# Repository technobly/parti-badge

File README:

# #PartiBadge

The #PartiBadge is a Wi-Fi connected, full-featured, Particle Photon powered conference badge. Because who want to wear a piece of plastic around their neck when they can wear a PCB?

The #PartiBadge was designed by the Particle team and is currently used as an interactive learning platform for conferences and other developer events.

For workshop hands-on labs and other details, click [here](https://bit.ly/tc-workshop).

The hardware folder contains Eagle design files for iterations of the badge hardware. The firmware folder contains firmware for the latest version of the badge.

The finished badge includes:

1. A 1" OLED Screen
2. An SMD Piezo buzzer
3. A SPDT Switch
4. A 5-way joystick
5. An SMD Si7021 temperature and Humidity sensor
6. 4 Tactile LED Buttons in Red, Blue, Green and Yellow/Orange
7. An I2C-Compatible breakout for #BadgeLife add-ons
8. An IR Receiver

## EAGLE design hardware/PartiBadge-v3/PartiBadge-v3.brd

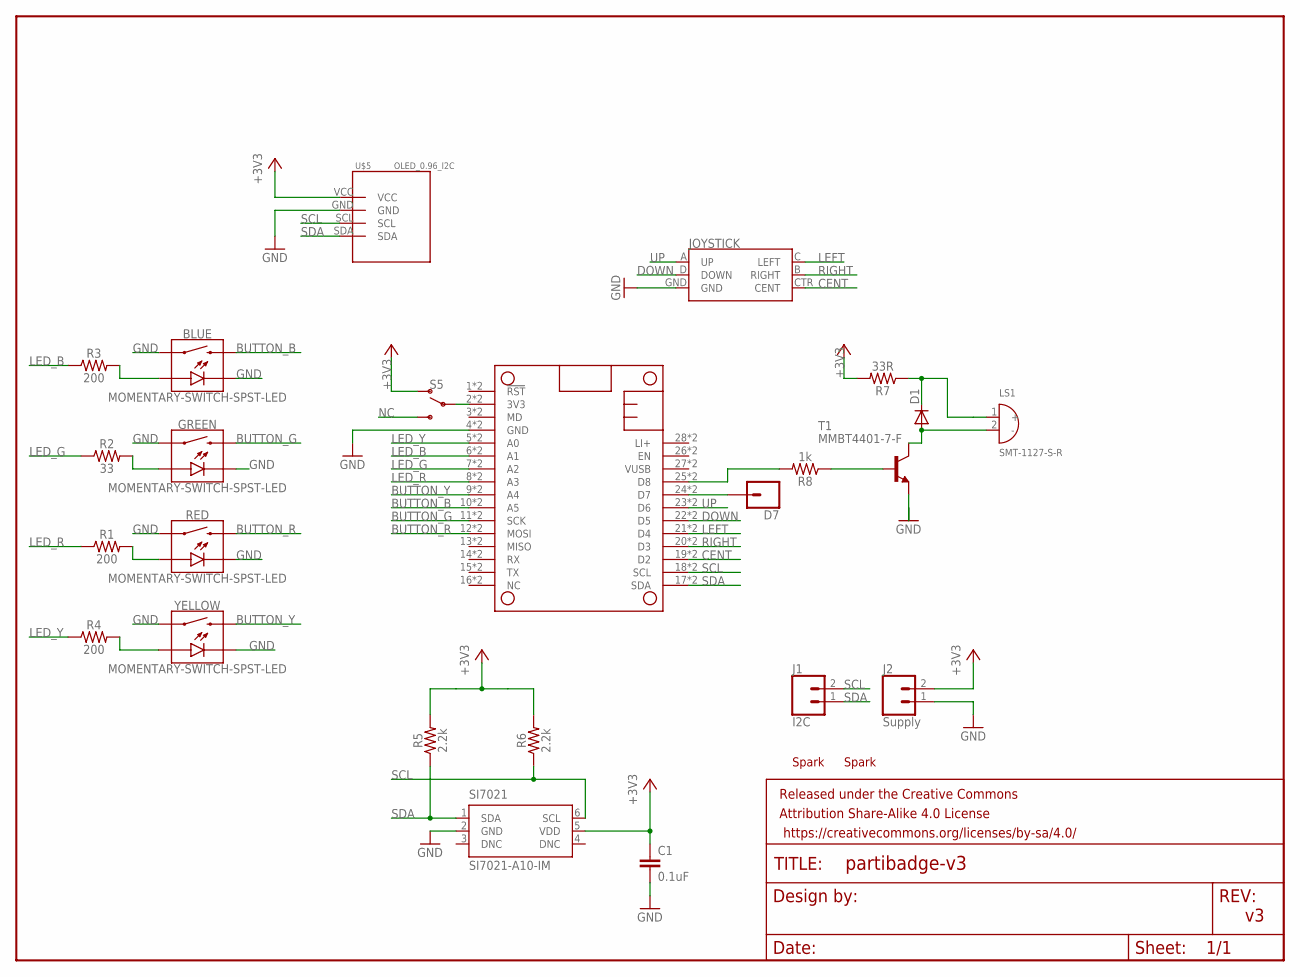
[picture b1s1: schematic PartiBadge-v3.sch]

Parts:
BLUE: MOMENTARY-SWITCH-SPST-LED; TACTILE_SWITCH_LED_PTH_12MM_KIT
C1: 0.1uF; 0603
D1: DIODE-SOD323-W; SOD323-W
D7: CONN_01; 1X01
GREEN: MOMENTARY-SWITCH-SPST-LED; TACTILE_SWITCH_LED_PTH_12MM_KIT
J1: I2C; 1X02
J2: Supply; 1X02
JOYSTICK: JOYSTICK_MINI
LS1: SMT-1127-S-R; XDCR_SMT-1127-S-R
MS1: PARTICLE_MESH_SMTDUAL; FEATHERWING_SMT2
PARTIFRAME: FRAME-LETTERNO_PACKAGE; DUMMY
R1, R3, R4: 200; 1206
R2: 33; 1206
R5, R6: 2.2k; 0603
R7: 33R; 0603
R8: 1k; 0603
RED: MOMENTARY-SWITCH-SPST-LED; TACTILE_SWITCH_LED_PTH_12MM_KIT
S5: SWITCH-SPDT-PTH-11.6X4.0MM; SWITCH_SPDT_PTH_11.6X4.0MM
SI7021: SI7021-A10-IM; DFN6-3X3
T1: MMBT4401-7-F; SOT23-BEC
U$1, U$2: SPARK_LOGO_WITH_PLANE; SPARK_LOGO_PLUS_PLANE
U$5: OLED_0.96_I2C
YELLOW: MOMENTARY-SWITCH-SPST-LED; TACTILE_SWITCH_LED_PTH_12MM_KIT

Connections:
3V3: MS1.2 (3V3), MS1.2' (3V3), S5.2
+3V3: C1.1, J2.2, R5.2, R6.2, R7.2, S5.1 (O), SI7021.5 (VDD), U$5.VCC
BUTTON_B: BLUE.2, MS1.10 (A5), MS1.10' (A5)
BUTTON_G: GREEN.2, MS1.11 (SCK), MS1.11' (SCK)
BUTTON_R: MS1.12 (MOSI), MS1.12' (MOSI), RED.2
BUTTON_Y: MS1.9 (A4), MS1.9' (A4), YELLOW.2
CENT: JOYSTICK.CTR (CENT), MS1.19 (D2), MS1.19' (D2)
DOWN: JOYSTICK.D (DOWN), MS1.22 (D5), MS1.22' (D5)
GND: BLUE.4 (1), BLUE.C, C1.2, GREEN.4 (1), GREEN.C, J2.1, JOYSTICK.GND, MS1.4 (GND), MS1.4' (GND), RED.4 (1), RED.C, SI7021.2 (GND), T1.E, U$5.GND, YELLOW.4 (1), YELLOW.C
LED_B: MS1.6 (A1), MS1.6' (A1), R3.1
LED_G: MS1.7 (A2), MS1.7' (A2), R2.1
LED_R: MS1.8 (A3), MS1.8' (A3), R1.1
LED_Y: MS1.5 (A0), MS1.5' (A0), R4.1
LEFT: JOYSTICK.C (LEFT), MS1.21 (D4), MS1.21' (D4)
unnamed: D7.1, MS1.24 (D7), MS1.24' (D7)
unnamed: MS1.25 (D8), MS1.25' (D8), R8.2
unnamed: R1.2, RED.A
unnamed: R8.1, T1.B
unnamed: GREEN.A, R2.2
unnamed: BLUE.A, R3.2
unnamed: R4.2, YELLOW.A
unnamed: D1.A, LS1.2 (-), T1.C
unnamed: D1.C, LS1.1 (+), R7.1
NC: S5.3 (S)
RIGHT: JOYSTICK.B (RIGHT), MS1.20 (D3), MS1.20' (D3)
SCL: J1.2, MS1.18 (SCL), MS1.18' (SCL), R6.1, SI7021.6 (SCL), U$5.SCL
SDA: J1.1, MS1.17 (SDA), MS1.17' (SDA), R5.1, SI7021.1 (SDA), U$5.SDA
UP: JOYSTICK.A (UP), MS1.23 (D6), MS1.23' (D6)

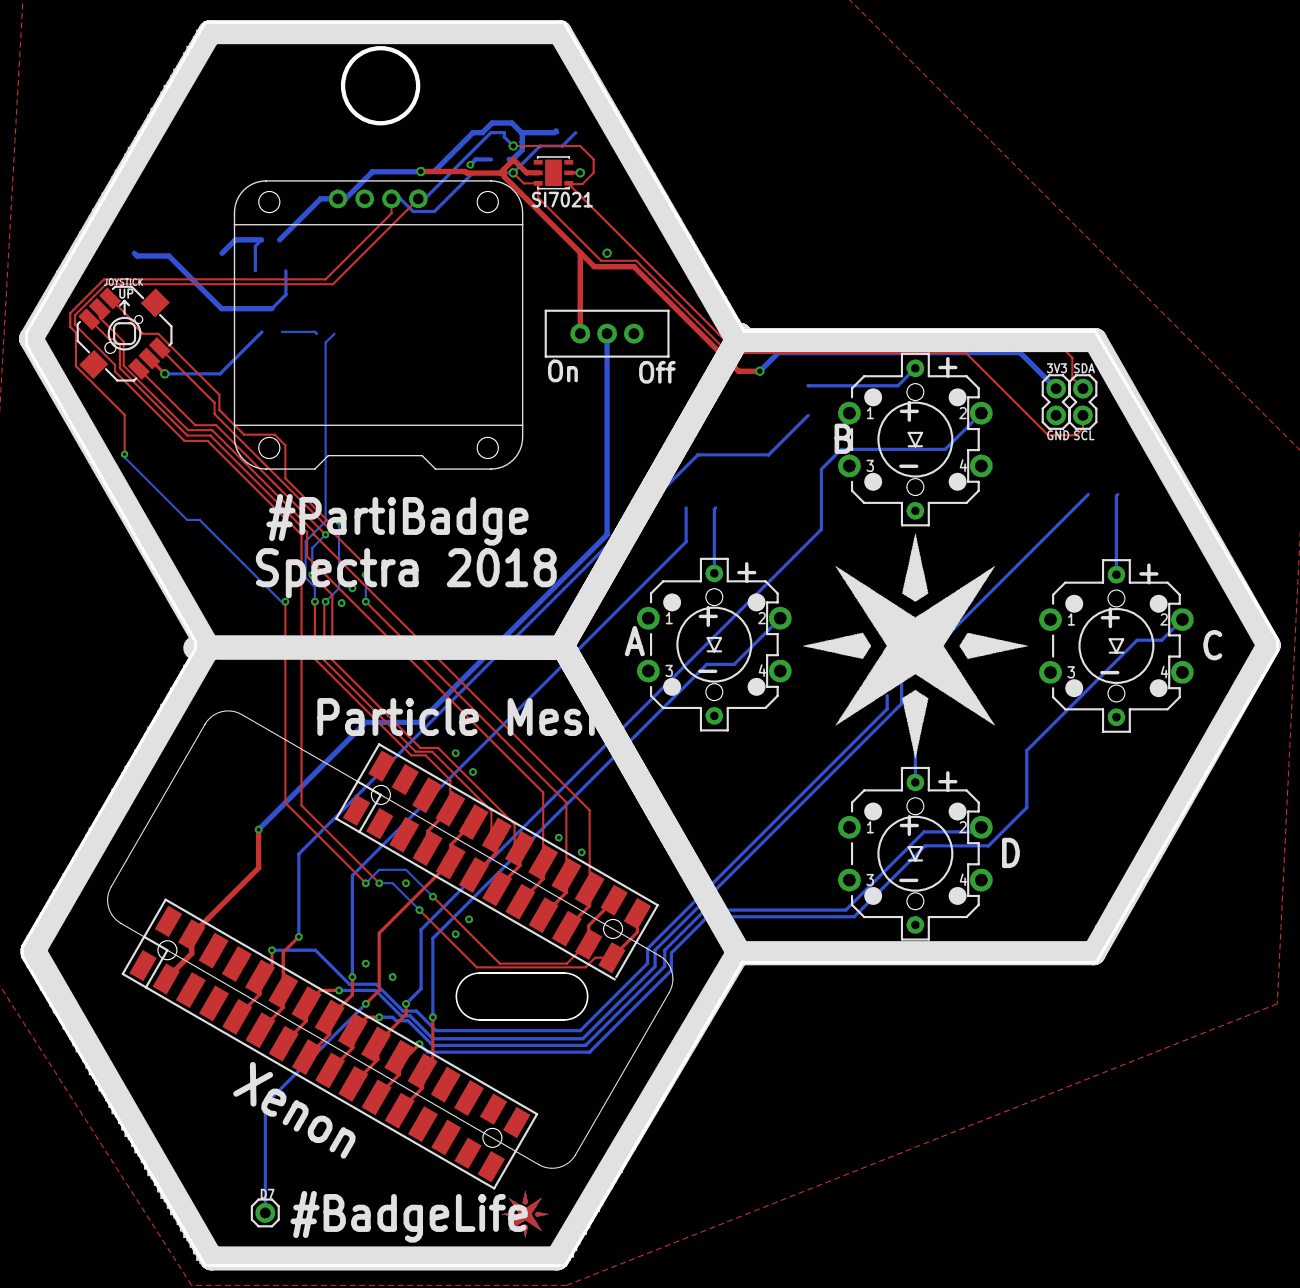
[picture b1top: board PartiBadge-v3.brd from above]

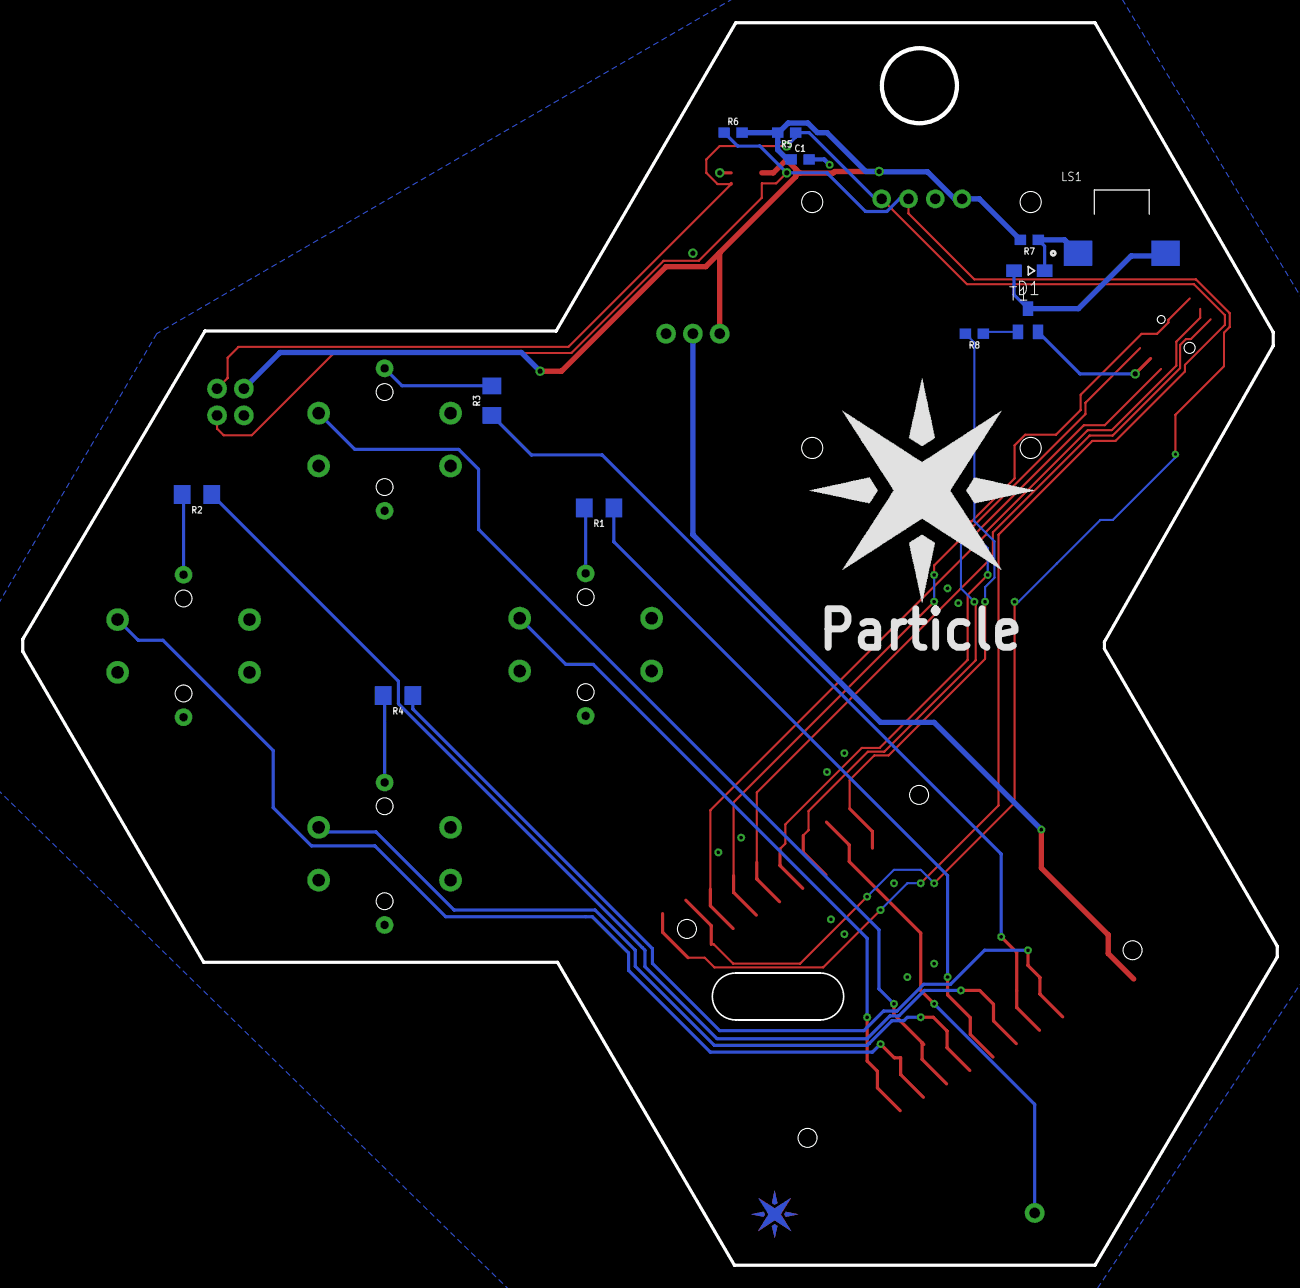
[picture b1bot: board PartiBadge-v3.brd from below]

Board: 4 copper layers, 118.9 x 117.7 mm, 30 parts (15 on the bottom side), 27 nets.

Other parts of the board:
U$3: MESH#1PX#SVG
U$4, U$6: SPARK-LOGO

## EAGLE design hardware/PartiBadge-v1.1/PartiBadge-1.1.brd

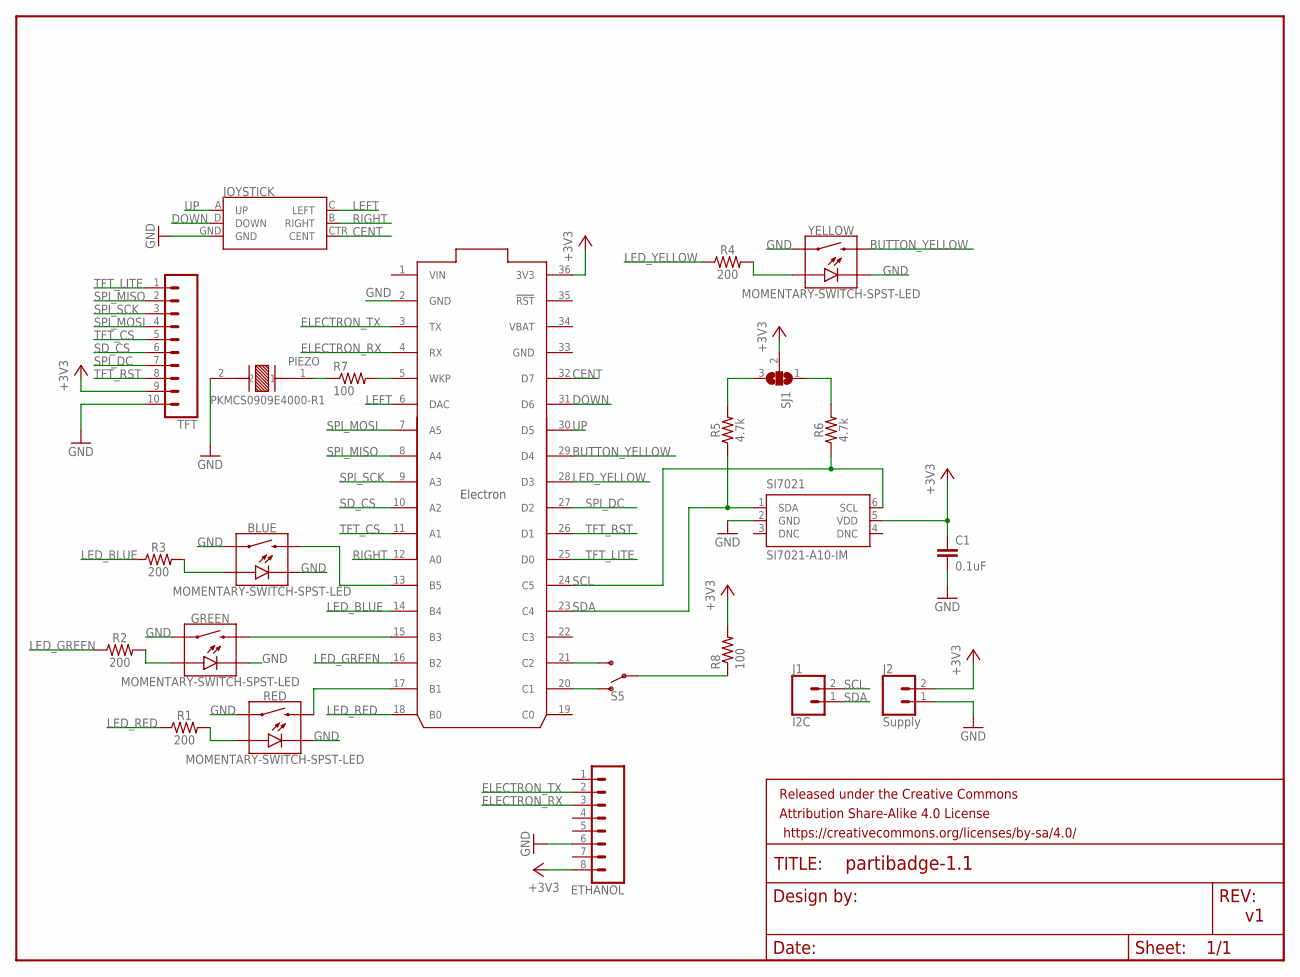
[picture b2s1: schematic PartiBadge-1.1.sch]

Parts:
BLUE: MOMENTARY-SWITCH-SPST-LED; TACTILE_SWITCH_LED_PTH_12MM_KIT
C1: 0.1uF; 0603
ELECTRON: ELECTRON_WITH_HEADERS; ELECTRON
ETHANOL: CONN_08"; 1X08
GREEN: MOMENTARY-SWITCH-SPST-LED; TACTILE_SWITCH_LED_PTH_12MM_KIT
J1: I2C; 1X02
J2: Supply; 1X02
JOYSTICK: JOYSTICK_MINI
PARTIFRAME: FRAME-LETTERNO_PACKAGE; DUMMY
PIEZO: PKMCS0909E4000-R1; XDCR_PKMCS0909E4000-R1
R1, R2, R3, R4: 200; 1206
R5, R6: 4.7k; 0603
R7, R8: 100; M0805
RED: MOMENTARY-SWITCH-SPST-LED; TACTILE_SWITCH_LED_PTH_12MM_KIT
S5: SWITCH-SPDT-PTH-11.6X4.0MM; SWITCH_SPDT_PTH_11.6X4.0MM
SI7021: SI7021-A10-IM; DFN6-3X3
SJ1: SJ2W; SJ_2
TFT: CONN_10NO_SILK_PTH_FEMALE; 1X10_NO_SILK
YELLOW: MOMENTARY-SWITCH-SPST-LED; TACTILE_SWITCH_LED_PTH_12MM_KIT

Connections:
3V3: C1.1, ELECTRON.36 (3V3), ETHANOL.8, J2.2, R8.2, SI7021.5 (VDD), SJ1.2, TFT.9
BUTTON_YELLOW: ELECTRON.29 (D4), YELLOW.2
CENT: ELECTRON.32 (D7), JOYSTICK.CTR (CENT)
DOWN: ELECTRON.31 (D6), JOYSTICK.D (DOWN)
ELECTRON_RX: ELECTRON.4 (RX), ETHANOL.3
ELECTRON_TX: ELECTRON.3 (TX), ETHANOL.2
GND: BLUE.4 (1), BLUE.C, C1.2, ELECTRON.2 (GND), ELECTRON.33 (GND), ETHANOL.6, GREEN.4 (1), GREEN.C, J2.1, JOYSTICK.GND, PIEZO.2, RED.4 (1), RED.C, SI7021.2 (GND), TFT.10, YELLOW.4 (1), YELLOW.C
LED_BLUE: ELECTRON.14 (B4), R3.1
LED_GREEN: ELECTRON.16 (B2), R2.1
LED_RED: ELECTRON.18 (B0), R1.1
LED_YELLOW: ELECTRON.28 (D3), R4.1
LEFT: ELECTRON.6 (DAC), JOYSTICK.C (LEFT)
unnamed: ELECTRON.5 (WKP), R7.2
unnamed: ELECTRON.20 (C1), S5.1 (O)
unnamed: ELECTRON.21 (C2), S5.3 (S)
unnamed: R1.2, RED.A
unnamed: ELECTRON.17 (B1), RED.2
unnamed: ELECTRON.15 (B3), GREEN.2
unnamed: GREEN.A, R2.2
unnamed: BLUE.A, R3.2
unnamed: BLUE.2, ELECTRON.13 (B5)
unnamed: R4.2, YELLOW.A
unnamed: R5.2, SJ1.3
unnamed: R6.2, SJ1.1
unnamed: PIEZO.1, R7.1
unnamed: R8.1, S5.2
RIGHT: ELECTRON.12 (A0), JOYSTICK.B (RIGHT)
SCL: ELECTRON.24 (C5), J1.2, R6.1, SI7021.6 (SCL)
SDA: ELECTRON.23 (C4), J1.1, R5.1, SI7021.1 (SDA)
SD_CS: ELECTRON.10 (A2), TFT.6
SPI_DC: ELECTRON.27 (D2), TFT.7
SPI_MISO: ELECTRON.8 (A4), TFT.2
SPI_MOSI: ELECTRON.7 (A5), TFT.4
SPI_SCK: ELECTRON.9 (A3), TFT.3
TFT_CS: ELECTRON.11 (A1), TFT.5
TFT_LITE: ELECTRON.25 (D0), TFT.1
TFT_RST: ELECTRON.26 (D1), TFT.8
UP: ELECTRON.30 (D5), JOYSTICK.A (UP)
VBAT: ELECTRON.34 (VBAT)
VIN: ELECTRON.1 (VIN)

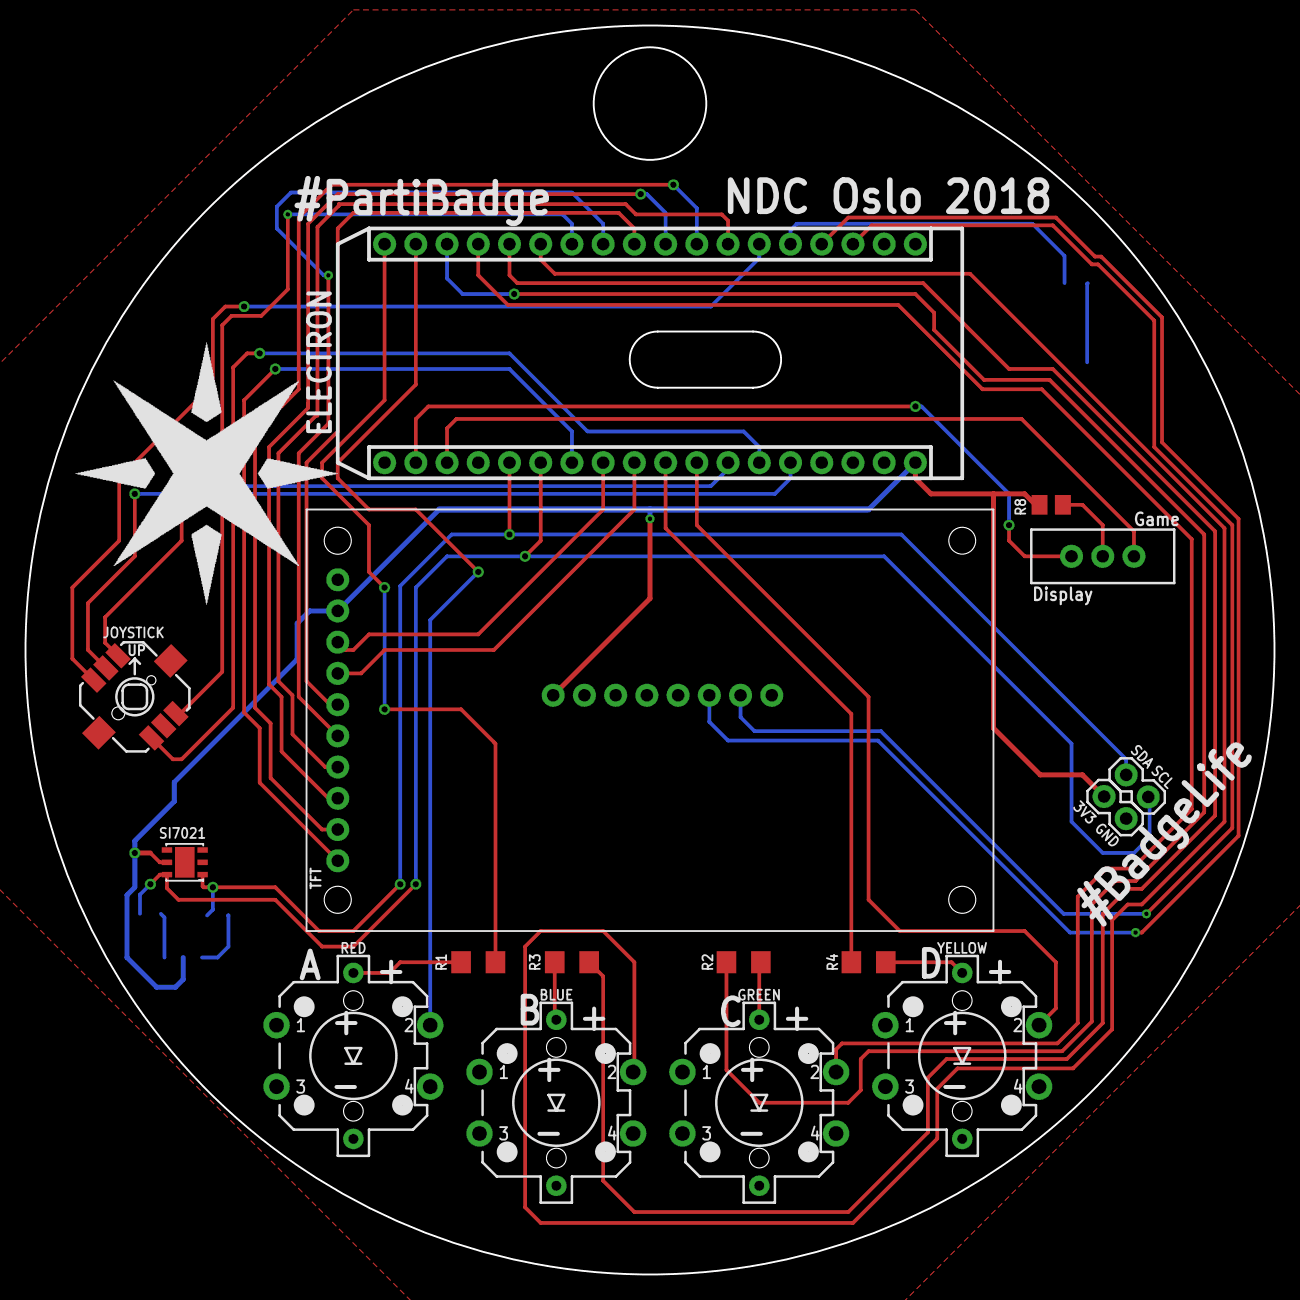
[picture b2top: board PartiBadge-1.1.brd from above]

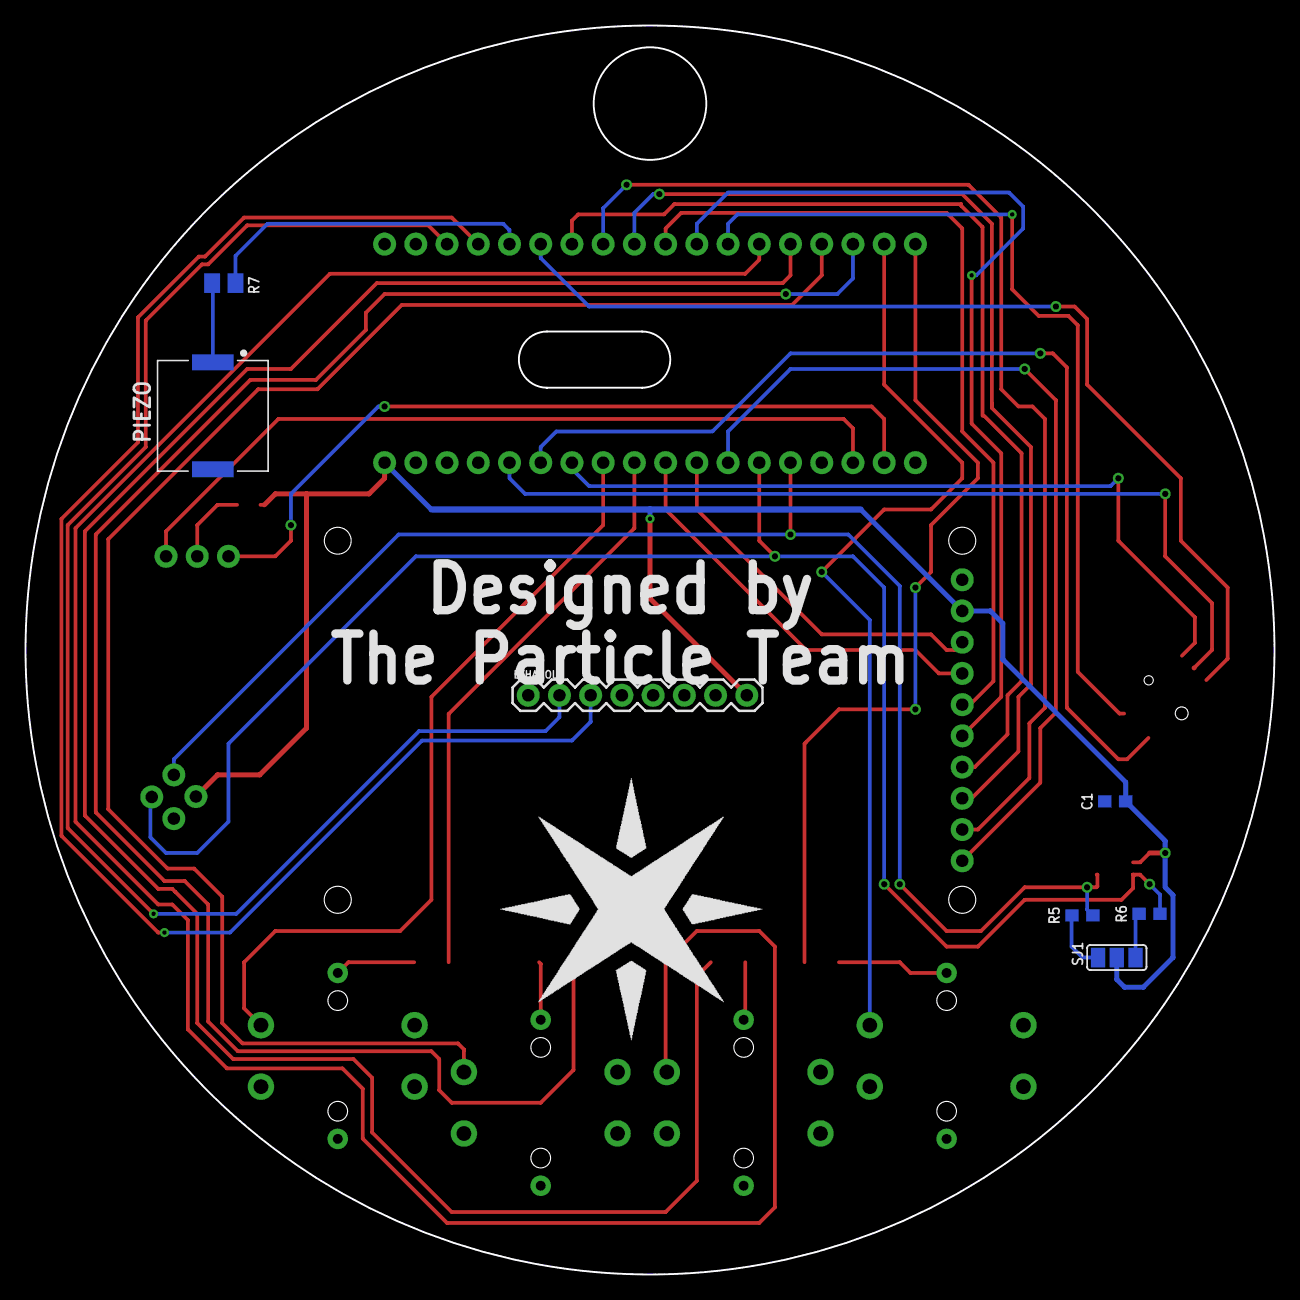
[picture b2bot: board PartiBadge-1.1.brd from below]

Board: 4 copper layers, 101.6 x 101.6 mm, 28 parts (8 on the bottom side), 38 nets.

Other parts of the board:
DRILEGEND: DRILEGEND
U$1, U$2: SPARK#PNG
U$3: FRAME_A_L

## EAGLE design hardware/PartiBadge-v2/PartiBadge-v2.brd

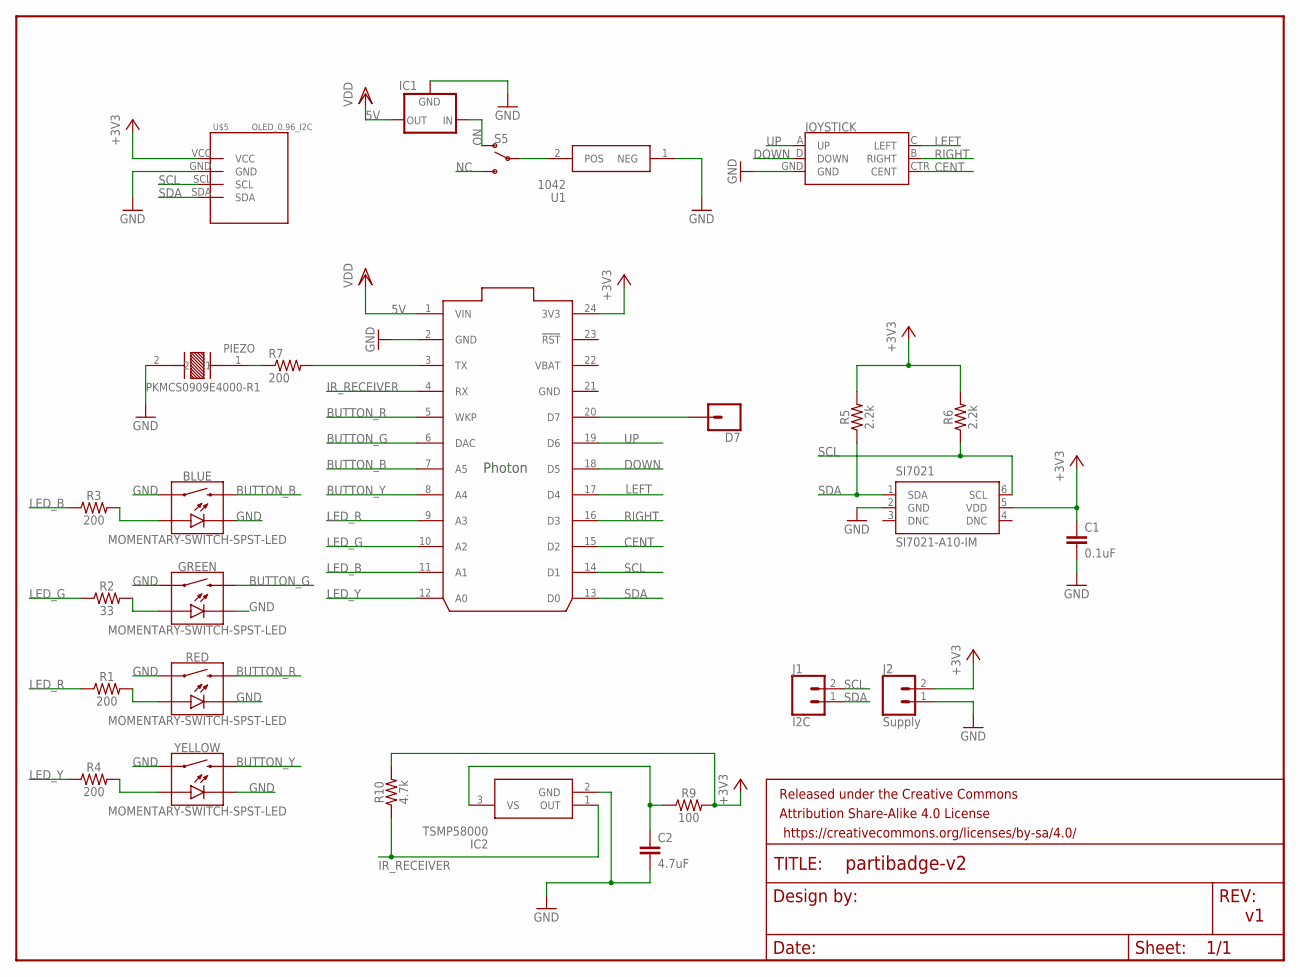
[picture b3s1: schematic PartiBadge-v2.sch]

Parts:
BLUE: MOMENTARY-SWITCH-SPST-LED; TACTILE_SWITCH_LED_PTH_12MM_KIT
C1: 0.1uF; 0603
C2: 4.7uF; 0603
D7: CONN_01; 1X01
GREEN: MOMENTARY-SWITCH-SPST-LED; TACTILE_SWITCH_LED_PTH_12MM_KIT
IC1: 78XXS
IC2: TSMP58000
J1: I2C; 1X02
J2: Supply; 1X02
JOYSTICK: JOYSTICK_MINI
PARTIFRAME: FRAME-LETTERNO_PACKAGE; DUMMY
PHOTON: PHOTON_WITH_HEADERS; PHOTON
PIEZO: PKMCS0909E4000-R1; XDCR_PKMCS0909E4000-R1
R1, R3, R4: 200; 1206
R2: 33; 1206
R5, R6: 2.2k; 0603
R7: 200; M0805
R9: 100; 1206
R10: 4.7k; 1206
RED: MOMENTARY-SWITCH-SPST-LED; TACTILE_SWITCH_LED_PTH_12MM_KIT
S5: SWITCH-SPDT-PTH-11.6X4.0MM; SWITCH_SPDT_PTH_11.6X4.0MM
SI7021: SI7021-A10-IM; DFN6-3X3
U1: 1042; KEYSTONE-1042
U$5: OLED_0.96_I2C
YELLOW: MOMENTARY-SWITCH-SPST-LED; TACTILE_SWITCH_LED_PTH_12MM_KIT

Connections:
5V: IC1.OUT, PHOTON.1 (VIN)
+3V3: C1.1, J2.2, PHOTON.24 (3V3), R5.2, R6.2, R9.2, R10.2, SI7021.5 (VDD), U$5.VCC
BATT: S5.2, U1.2 (POS)
BUTTON_B: BLUE.2, PHOTON.7 (A5)
BUTTON_G: GREEN.2, PHOTON.6 (DAC)
BUTTON_R: PHOTON.5 (WKP), RED.2
BUTTON_Y: PHOTON.8 (A4), YELLOW.2
CENT: JOYSTICK.CTR (CENT), PHOTON.15 (D2)
D7: D7.1, PHOTON.20 (D7)
DOWN: JOYSTICK.D (DOWN), PHOTON.18 (D5)
GND: BLUE.4 (1), BLUE.C, C1.2, C2.2, GREEN.4 (1), GREEN.C, IC1.GND, IC2.2 (GND), J2.1, JOYSTICK.GND, PHOTON.2 (GND), PHOTON.21 (GND), PIEZO.2, RED.4 (1), RED.C, SI7021.2 (GND), U1.1 (NEG), U$5.GND, YELLOW.4 (1), YELLOW.C
IR_RECEIVER: IC2.1 (OUT), PHOTON.4 (RX), R10.1
LED_B: PHOTON.11 (A1), R3.1
LED_G: PHOTON.10 (A2), R2.1
LED_R: PHOTON.9 (A3), R1.1
LED_Y: PHOTON.12 (A0), R4.1
LEFT: JOYSTICK.C (LEFT), PHOTON.17 (D4)
unnamed: PHOTON.3 (TX), R7.2
unnamed: R1.2, RED.A
unnamed: GREEN.A, R2.2
unnamed: BLUE.A, R3.2
unnamed: C2.1, IC2.3 (VS), R9.1
unnamed: R4.2, YELLOW.A
unnamed: PIEZO.1, R7.1
NC: S5.3 (S)
ON: IC1.IN, S5.1 (O)
RIGHT: JOYSTICK.B (RIGHT), PHOTON.16 (D3)
SCL: J1.2, PHOTON.14 (D1), R6.1, SI7021.6 (SCL), U$5.SCL
SDA: J1.1, PHOTON.13 (D0), R5.1, SI7021.1 (SDA), U$5.SDA
UP: JOYSTICK.A (UP), PHOTON.19 (D6)
VBAT: PHOTON.22 (VBAT)

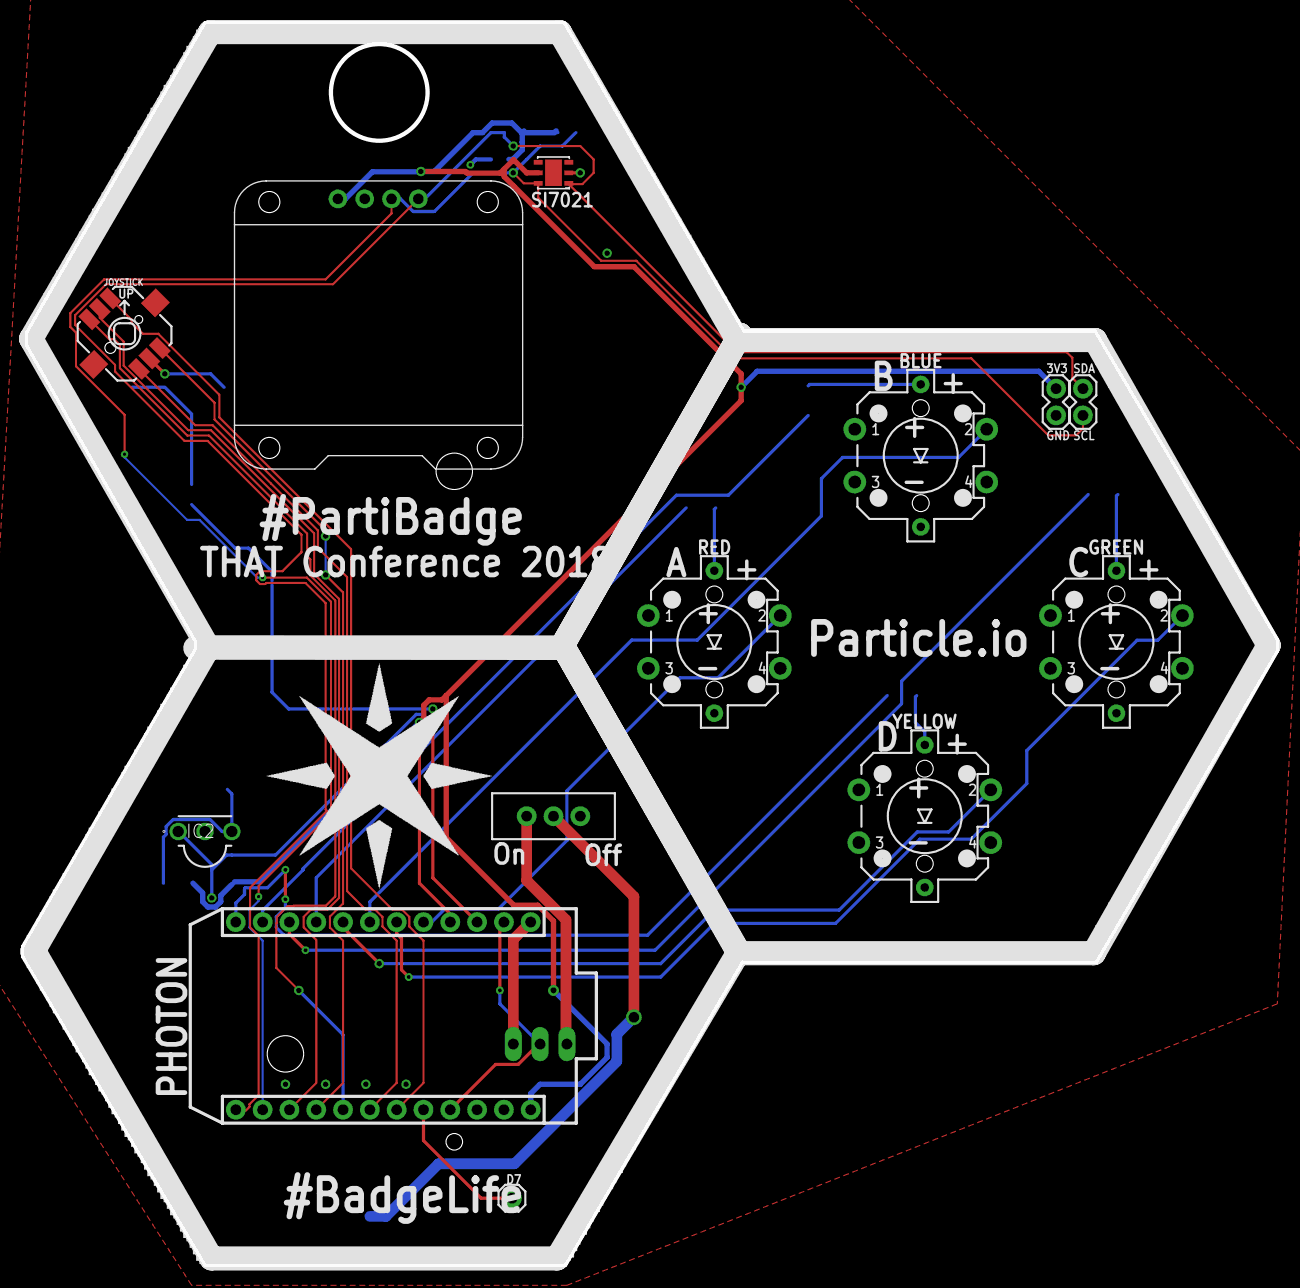
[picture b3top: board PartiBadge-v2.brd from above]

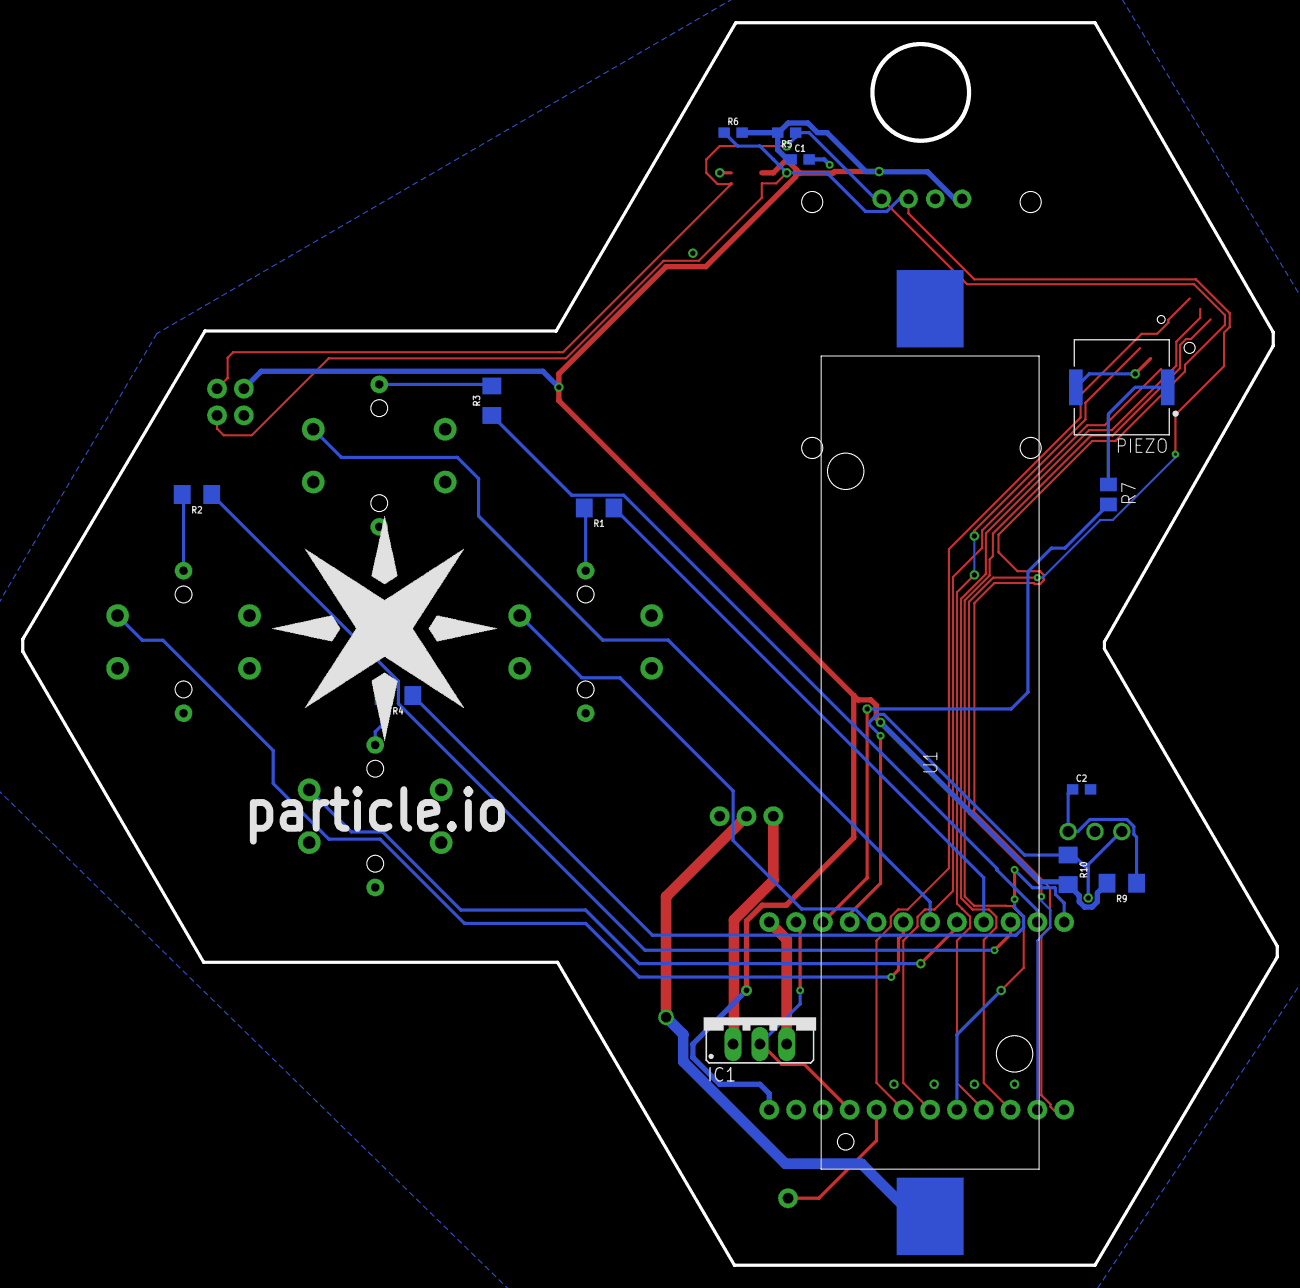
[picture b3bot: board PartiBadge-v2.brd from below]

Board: 4 copper layers, 118.9 x 117.7 mm, 31 parts (16 on the bottom side), 29 nets.

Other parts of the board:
U$1, U$4: SPARK-LOGO
U$3: MESH#1PX#SVG

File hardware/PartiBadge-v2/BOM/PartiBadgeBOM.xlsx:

Part Desc | Footprint names | Reference Part # | Ordered From | Per Badge Cost | # Ordered | Delivery By | # On hand | # Needed for Badge
SMD 4.7K OHM 1% 1/10W 1206 Resistor | R10 |  | Digi-Key |  |  |  | 90 | 100
SMD 2.2k OHM 1% 1/16W 1206 Resistor | R5, R6 |  | Digi-Key |  |  |  | 100 | 200
SMD 200 OHM 5% 1/4W 0805 Resistor | R7 |  | Digi-Key |  |  |  | 98 | 100
SMD 100 OHM 0.1% 1/4W 1206 | R9 |  | Digi-Key |  |  |  | 100 | 100
SMD 200 OHM 0.1% 1/4W 1206 | R1, R3, R4 |  | Digi-Key |  |  |  | 95 | 300
SMD 33 OHM 0.5% 1W 1206 | R2 |  | Digi-Key |  |  |  | 10 | 100
0.1uF 25V 0603 Ceramic Capacitor | C1 |  | Digi-Key |  |  |  | 70 | 100
4.7UF 10V X7S 0603 Ceramic Capacitor | C2 |  | Digi-Key |  |  |  | 100 | 100
Silicon Labs SI7021-A20-IM HU/Temp Sensor 3.6V I2C 3% 6DFN | SI7021 | 336-3142-5-ND | Digi-Key |  |  |  | 10 | 100
Murata Electronics AUDIO PIEZO TRANSDUCER 12.5V SMD (PKMCS0909E4000-R1) | PIEZO | 490-9647-1-ND | Digi-Key |  |  |  | 15 | 100
E-Switch SWITCH SLIDE SPDT 200MA 30V | S5 | EG1903-ND | Digi-Key |  |  |  | 5 | 100
LED Tactile Button - Green | GREEN | COM-10440 | Sparkfun |  |  |  | 4 | 100
LED Tactile Button - Orange | YELLOW | COM-10441 | Sparkfun |  |  |  | 4 | 100
LED Tactile Button - Red | RED | COM-10442 | Sparkfun |  |  |  | 4 | 100
LED Tactile Button - Blue | BLUE | COM-10443 | Sparkfun |  |  |  | 4 | 100
5-way Tactile Switch | JOYSTICK | COM-10063 | Sparkfun |  |  |  | 1 (+10 OTW) | 100
Vishay Semiconductor TSMP IR Detector | IC2 | TSMP58000-ND | Digi-Key |  |  |  | 10 | 100
WorldChips 0.96" OLED Display | U$5 | SSD1306 | AliExpress |  |  |  | OTW | 100
LiiToKala Li-On 3.7v 3400mAh Battery |  | 18650 | AliExpress |  |  |  | OTW | 100
Keystone Electronics 1042 Battery Clip | U1 | 36-1042-ND | Digi-Key |  |  |  | 10 | 100
Pololu 5V Step-Up Voltage Regulator U3V12F5 | IC1 | 2115 | Pololu |  |  |  | OTW | 100
12 Position Female Header | Photon Headers | S6100-ND | Digi-Key |  |  |  | OTW | 200
Badge BOM Total

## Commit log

2018-05-02 cleaned up animations, implemented tweet notifications & fix OLED display issues
2018-05-02 updated to use ported SSD library
2018-05-02 initial port of badge code to photon
2018-05-02 tweak layout for smaller badge
2018-05-02 schematic and board v1
2018-05-02 moved firmware into folder
2018-05-02 increase text and add clr on piezo
2018-05-02 added tft mounting holes
2018-05-03 added frame and cleaned up schematic; added 5-way joystick
2018-05-03 routed board. closes #3 and #4
2018-05-04 added slot for lipo and antenna; closes #7
2018-05-04 Add clr to 3v3 line next to switch; closes #9; add text to back; closes #8
2018-05-04 fix schematic and board with clr
2018-05-04 cleaning up routes
2018-05-04 route and via cleanup; closes #11
2018-05-04 rear-side logo positioning
2018-05-04 fix right-angle routes; closes #13
2018-05-04 added ground plane to top; closes #16
2018-05-04 increase size of slot; closes #15
2018-05-04 smash ref designators and clean up refs; closes #14
2018-05-04 added A, B, C, D to silk; closes #17
2018-05-04 move the spark logo
2018-05-04 tented vias; closes #19
2018-05-04 re-tented the accidentally untented vias
2018-05-04 generated gerbers
2018-05-07 final updates for fabrication
2018-05-08 wired up switch to toggle between display and game mode; closes #35
2018-05-09 wired up piezo buzzer; closes #39
2018-05-09 bodge Piezo by shorting C0 to WKP/A7 until #40 can be addressed
2018-05-09 add variables and subscriptions for wearer info; closes #37
2018-05-09 tft hookup done (#43), but having some trouble with display. Going to move on for a bit.
2018-05-10 working on temp sensor
2018-05-10 aded Si7021 Temp/Hu support; closes #44
2018-05-10 added device cloud variables for temp and hunmidity; closes #33
2018-05-10 check temp and humidity on an interval; closes #34
2018-05-10 check battery every five min; closes #45
2018-05-10 implement piezo buzz and shutoff when battery is critical; closes #28
2018-05-11 wired up tft and added startup text; closes #43
2018-05-11 wired up LED buttons; closes #42
2018-05-11 show temp and hu when A button is pressed; closes #31
2018-05-11 show battery % when B is pressed; closes #30
2018-05-14 wired up tactile switch; closes #47. started to organize loop around modes
2018-05-14 show lobatt warning; closes #29
2018-05-14 clean up startup state management
2018-05-14 display wearer on tft; closes #36
2018-05-16 wired up sd; closes #49
2018-05-17 Added simon says code; closes #27
2018-05-17 working on displaying images
2018-05-18 display spark on startup; closes #48
2018-05-18 rotate mesh images; closes #48; closes #38
2018-05-18 added more mesh images
2018-05-18 finish secret feature support
2018-05-23 moved piezo pin in schematic; closes #41
2018-05-23 moved tft cs pin; closes #50
2018-05-23 rev partibadge hardware for ndc oslo
2018-06-04 updated schematic and board
2018-06-13 added badge v2 design
2018-06-17 revisions to brd v2
2018-06-19 final update before initial fab run
2018-06-20 fixed power routing and made 3V3 traces wider
2018-06-20 widened traces from batt to converter
2018-06-20 removed gerbers
2018-06-29 fix v2 board issues
2018-07-01 mode switch to power and other cosmetic changes
2018-07-01 added board stackup and cosmetic fixes
2018-07-02 updated schematic and layout based on feedback from Brett
2018-07-02 additional layout tweaks
2018-07-02 added vias for ground plane
2018-07-02 fix D7 breakout placement
2018-07-02 added BOM
2018-07-03 added v2 gerbers
2018-07-11 initial cleanup with working startup on the Photon
2018-07-13 implement mode switch with buttons, fixed simon-says; closes #71; closes #68
2018-07-13 fixed hu/temp formatting; closes #78
2018-07-13 implemented OLED; closes #72
2018-07-17 added Particle logo splashscreen; closes #79
2018-07-18 added title screen; closes #80
2018-07-18 added temp and hu to display
2018-07-18 update temp/hu on change when displayed
2018-07-18 implemented new rickroll
2018-07-19 show spark on screen during roll; closes #87
2018-07-19 re-implemented showing wearer details
2018-07-22 added ability to store wearer info in EEPROM
2018-07-22 added images to temp/hu screen
2018-07-23 added named event
2018-07-23 update display when name updates
2018-07-23 added score to display for simon says
2018-07-26 clean up event publishing
2018-07-26 added animation support
2018-07-27 split up temp and hu events
2018-07-31 implemented etch-a-sketch mode
2018-08-02 implemented konami code logger. Closes #26
2018-08-02 remove serial prints
2018-08-03 add konami logo to event
2018-08-03 implemented IR detector; closes #69
2018-08-03 added display messages when ir codes are captured
2018-08-04 cleaned up source, added comments and README
2018-08-05 move this back to earlier in setup to avoid race condition (flickering display)
2018-08-07 Update with Twitter info.
2018-08-23 added Xenon-based v3 design
2018-08-23 swapped out npn transistor
2018-08-23 added transistor to layout
2018-08-24 finished Xenon port
2018-08-27 piezo tweak from Frank
2018-09-06 finalized v3 design
2018-09-06 tweak text
2018-09-07 regenerate gerbers
2018-09-11 intial implementation of screen menu system
2018-09-11 tweak title screen
2018-09-11 fixed temp/hu display for two-color screen
2018-09-11 fix spark logo for two-color screen
2018-09-11 refactor out display methods
2018-09-11 continue building out sub-menus on display
2018-09-12 implemented etch-a-sketch on new menu mode
2018-09-13 refactored simon says game and music files
2018-09-13 cleaned up beegees music code
2018-09-13 update display bools logic to handle cloud function updates
2018-09-16 added graphics menu and items
2018-09-17 moved inputs into a module
2018-09-18 refactored out sensors code
2018-09-18 updated .gitignore
2018-09-18 Refactor roll audio; closes #127
2018-09-19 Cleaned-up events code
2018-09-19 add pwm fade for LEDs
2018-09-19 implemented snake game; closes #129
2018-09-19 fix scrolling of konami logo; closes #131
2018-09-19 added mesh graphic; closes #130
2018-09-20 change pin-mapping for xenon
2018-09-20 remove EEPROM calls to save wearer info
2018-09-20 removed SYSTEM_MODE call
2018-09-20 implemented animations; closes #132
2018-09-20 event header ifdef bug
2018-09-20 added pulsing led animation; Closes #135
2018-09-20 implemented chase blinky; closes #134
2018-09-21 add spectra logo; closes #150
2018-09-21 added carousel function
2018-09-21 added carousel to blinky animations
2018-09-24 put EEPROM code back in place; closes #149
2018-09-25 improved light animations; closes #146
2018-09-25 removed simon says code
2018-09-25 added battery status; closes #126
2018-09-26 added UDP demo
2018-09-26 stub out mesh send event for tower
2018-09-26 Started implementing hello ping. Fixed buttons; closes #152
2018-09-26 added Red and Green button interrupts back; closes #155
2018-09-26 started implementing mesh network details for #123
2018-09-26 working on mesh receive events for #142
2018-09-26 implement Mesh events for #141 and #142
2018-09-27 added battery image to screen; for #154
2018-09-27 add logic to turn on buttons when pressed; for #143
2018-09-27 remove button light state
2018-09-27 implemented battery graphic; closes #154
2018-09-27 continue work on mesh pub/sub
2018-09-28 tweaking button interactions for #143
2018-09-28 added modular binaries
2018-09-28 added system-part binary
2018-09-28 implemented mesh pub/sub events; closes #141 and #142
2018-09-29 re-implement semi-automatic mode; closes #153
2018-09-29 added lab events; closes #156
2018-09-29 updated firmware binaries
2018-09-29 re-implemented simon says mode; closes #145
2018-09-29 turn on buttons when pressed; closes #143
2018-09-29 added LED animations during music menu plays; closes #128
2018-10-01 implemented mesh network details for #123. Needs to be tested
2018-10-01 updated application firmware
2018-10-01 clean-up readme and tweak .gitignore
2018-10-01 complete implementing mesh details; closes #123
2018-10-01 updated binaries
2018-10-01 updated app binaries
2018-10-01 update main bin
2018-10-02 tweak and finalize spectra firmware
2018-10-18 added spooky mesh demo
2018-12-14 added holiday songs to badge
2019-02-16 Particle Sumo Bot - RC Control
2019-02-16 Speed up refresh time of display by 400%
2019-02-16 Fixed Particle Logo
2019-02-16 Update README.md for Particle Sumo Bot
2019-02-23 Added Logo Turtle OS Control

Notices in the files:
parts and their libraries:
SparkFun-Switches: Licensing: Creative Commons ShareAlike 4.0 International - https://creativecommons.org/licenses/by-sa/4.0
si70xx-10: (c) 2014 Samuel Lourenço
Particle-Devices: Licensing: Designed by Particle.
SparkFun-Aesthetics: https://creativecommons.org/licenses/by-sa/4.0
